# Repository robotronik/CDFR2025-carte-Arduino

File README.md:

# cdfr2025-carte-Arduino
Arduino mega pro Shield for CDFR 2025

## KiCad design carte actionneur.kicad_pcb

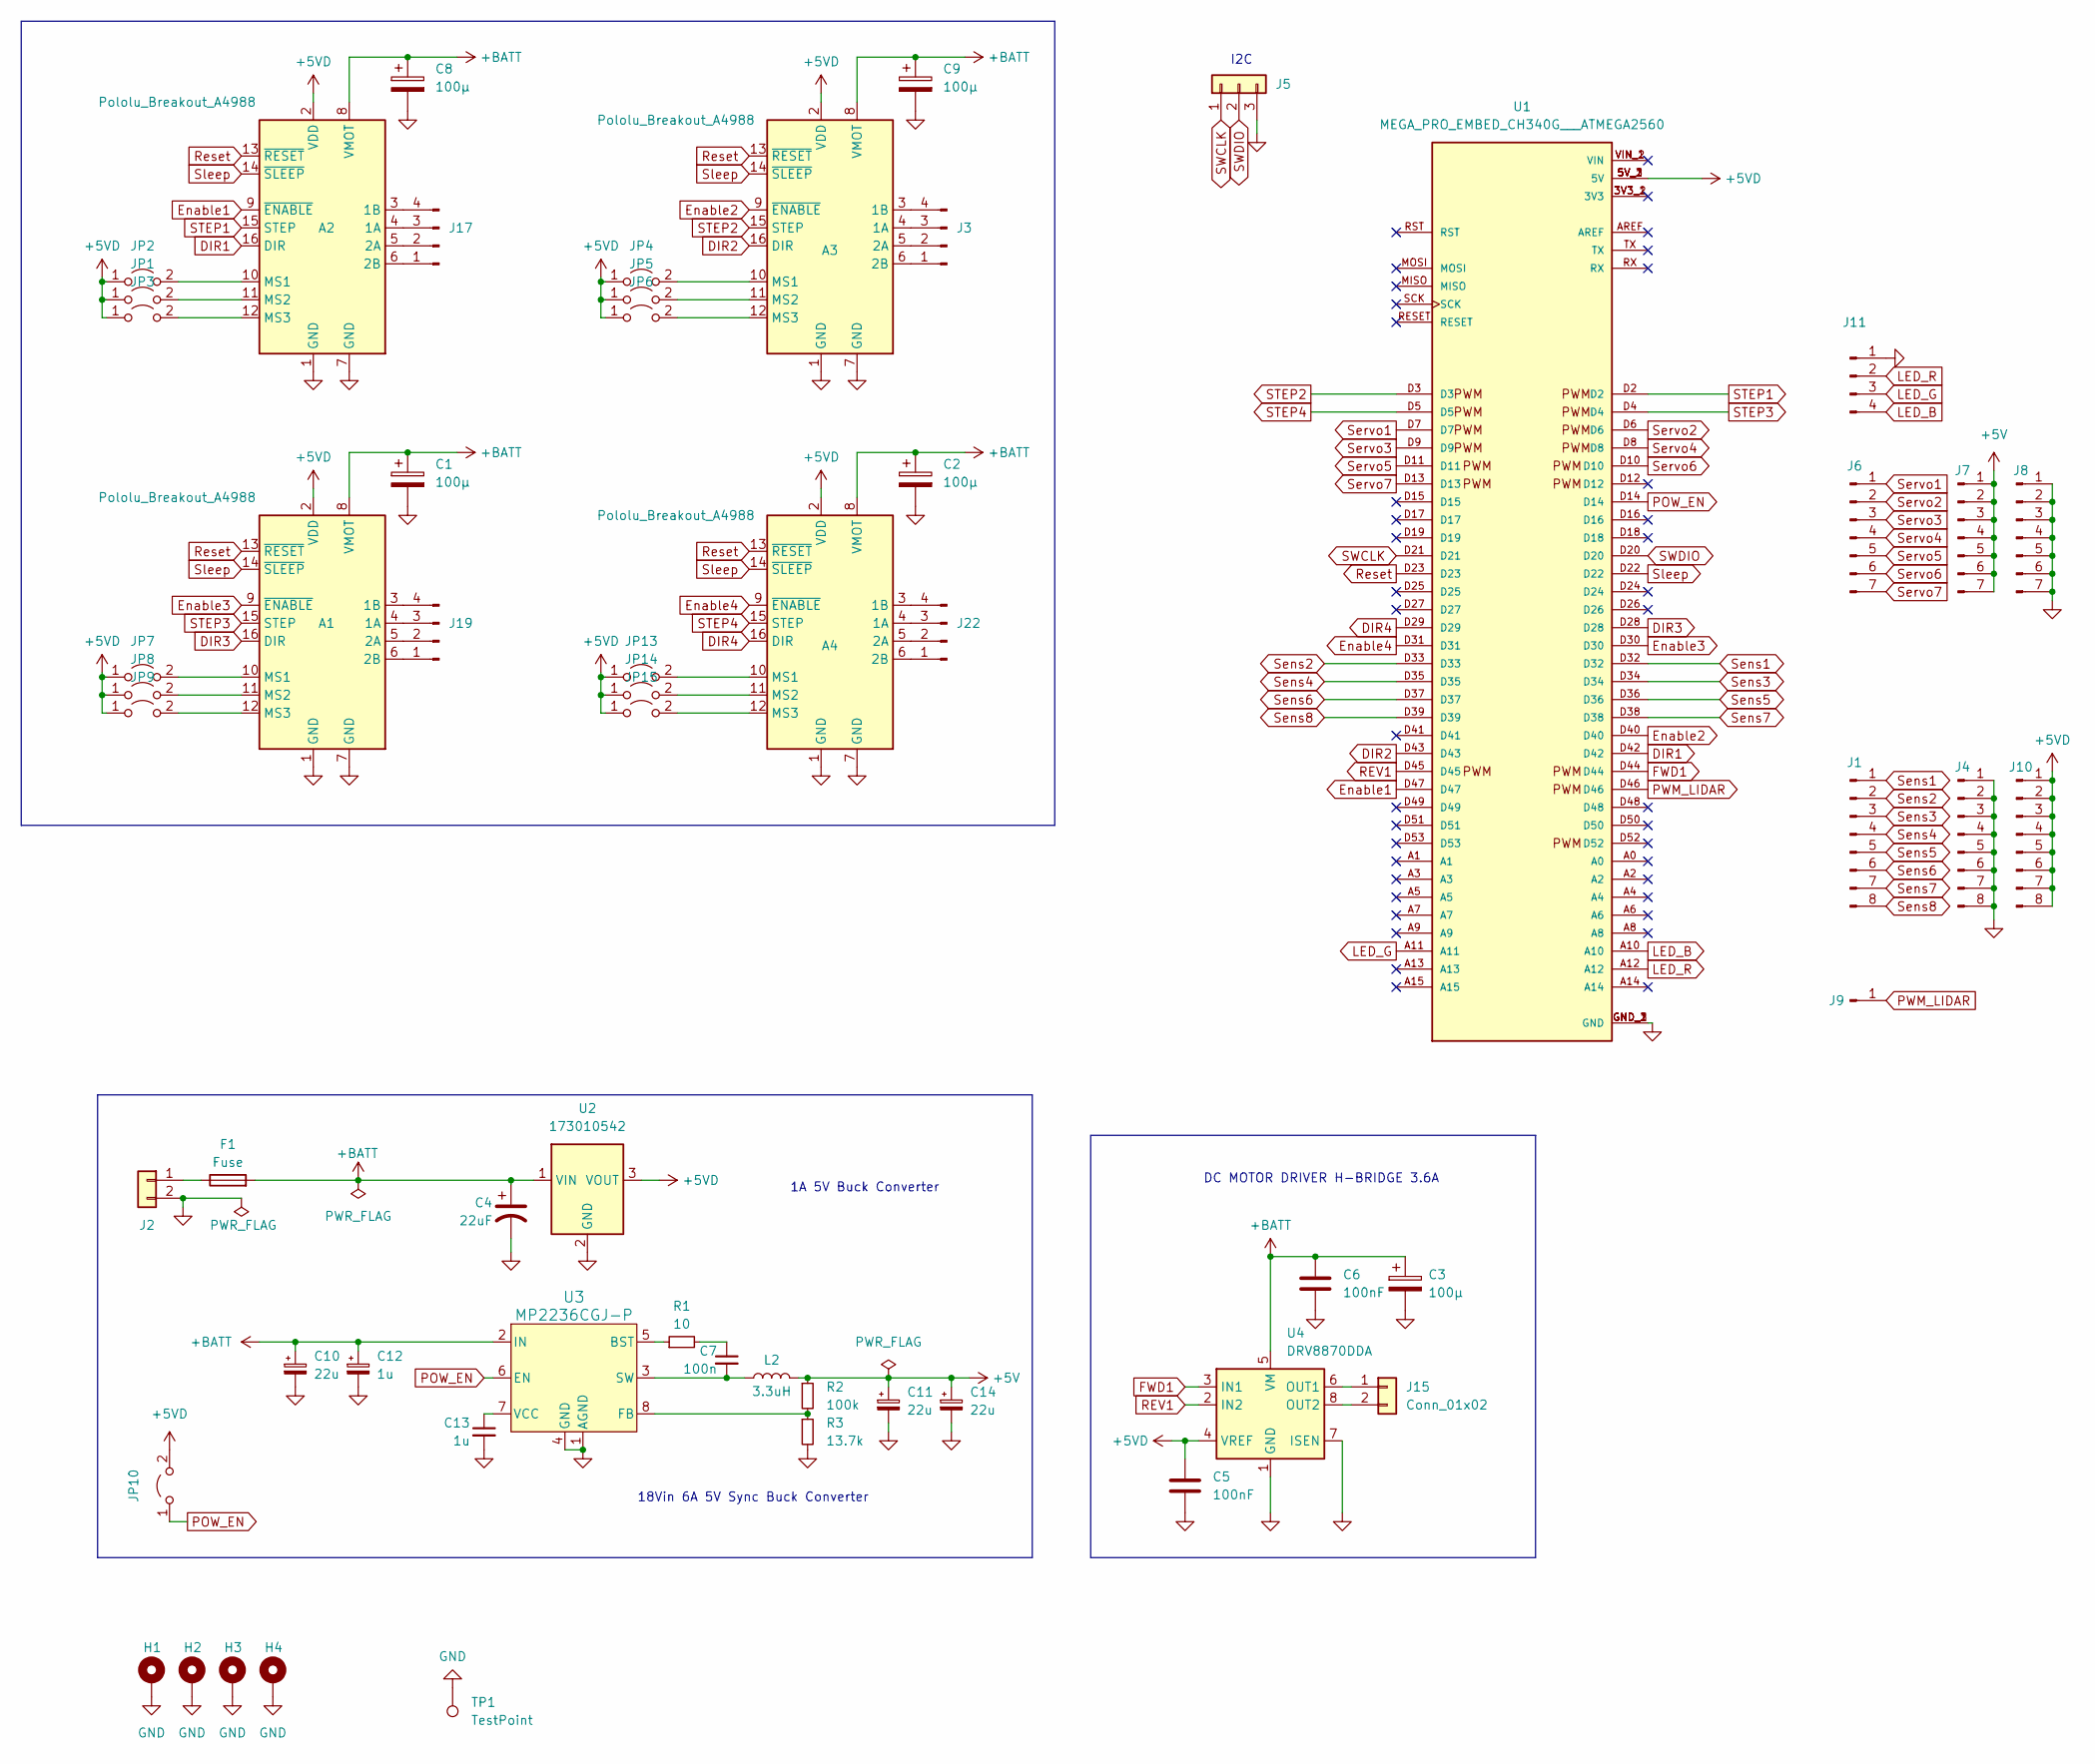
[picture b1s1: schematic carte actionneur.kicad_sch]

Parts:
A1, A2, A3, A4: Pololu_Breakout_A4988; Pololu_Breakout-16_15.2x20.3mm
C1, C2, C3, C8, C9: 100µ; CP_Radial_D8.0mm_P3.50mm
C4: 22uF; C_1206_3216Metric
C5, C6: 100nF; C_0805_2012Metric
C7: 100n; C_1206_3216Metric
C10, C11, C14: 22u; C_1206_3216Metric
C12, C13: 1u; C_1206_3216Metric
F1: Fuse; FUSE_0154004.DR
H1, H2, H3, H4: MountingHole_Pad; MountingHole_3.2mm_M3_Pad_Via
J1, J4, J10: Conn_01x08_Pin; PinHeader_1x08_P2.54mm_Vertical
J2: Conn_01x02; CUI_TBP01R1-508-02BE
J3, J17, J19, J22: Conn_01x04_Pin; JST_XH_B4B-XH-A_1x04_P2.50mm_Vertical
J5: Conn_01x03; JST_XH_B3B-XH-A_1x03_P2.50mm_Vertical
J6, J7, J8: Conn_01x07_Pin; PinHeader_1x07_P2.54mm_Vertical
J9: Conn_01x01_Pin; PinHeader_1x01_P2.54mm_Vertical
J11: Conn_01x04_Pin; PinHeader_1x04_P2.54mm_Vertical
J15: Conn_01x02; JST_XH_B2B-XH-A_1x02_P2.50mm_Vertical
JP1, JP2, JP3, JP4, JP5, JP6, JP7, JP8, JP9, JP10, JP13, JP14, JP15: Jumper_2_Open; SolderJumper-2_P1.3mm_Open_TrianglePad1.0x1.5mm
L2: 3.3uH; L_Coilcraft_XAL6030-XXX
R1: 10; R_1206_3216Metric
R2: 100k; R_1206_3216Metric
R3: 13.7k; R_0805_2012Metric
TP1: TestPoint; TestPoint_Bridge_Pitch2.0mm_Drill0.7mm
U1: MEGA_PRO_EMBED_CH340G___ATMEGA2560; MODULE_MEGA_PRO_EMBED_CH340G___ATMEGA2560; PARTREV 12/May/2017
U2: 173010542; U_Wurth_MagIC-FDSM_173010x42
U3: MP2236CGJ-P; TSOT-23-8
U4: DRV8870DDA; Texas_HTSOP-8-1EP_3.9x4.9mm_P1.27mm_EP2.95x4.9mm_Mask2.4x3.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

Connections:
+5V: C11.1, C14.1, J7.1, J7.2, J7.3, J7.4, J7.5, J7.6, J7.7, L2.2, R2.1
+5VD: A1.2 (VDD), A2.2 (VDD), A3.2 (VDD), A4.2 (VDD), C5.1, J10.1, J10.2, J10.3, J10.4, J10.5, J10.6, J10.7, J10.8, JP1.1 (A), JP2.1 (A), JP3.1 (A), JP4.1 (A), JP5.1 (A), JP6.1 (A), JP7.1 (A), JP8.1 (A), JP9.1 (A), JP10.2 (B), JP13.1 (A), JP14.1 (A), JP15.1 (A), U1.5V_1 (5V), U1.5V_2 (5V), U1.5V_3 (5V), U2.3 (VOUT), U4.4 (VREF)
+BATT: A1.8 (VMOT), A2.8 (VMOT), A3.8 (VMOT), A4.8 (VMOT), C1.1, C2.1, C3.1, C4.1, C6.1, C8.1, C9.1, C10.1, C12.1, F1.2, U2.1 (VIN), U3.2 (IN), U4.5 (VM)
DIR1: A2.16 (DIR), U1.D42
DIR2: A3.16 (DIR), U1.D43
DIR3: A1.16 (DIR), U1.D28
DIR4: A4.16 (DIR), U1.D29
Enable1: A2.9 (~ENABLE), U1.D47
Enable2: A3.9 (~ENABLE), U1.D40
Enable3: A1.9 (~ENABLE), U1.D30
Enable4: A4.9 (~ENABLE), U1.D31
FWD1: U1.D44, U4.3 (IN1)
GND: A1.1 (GND), A1.7 (GND), A2.1 (GND), A2.7 (GND), A3.1 (GND), A3.7 (GND), A4.1 (GND), A4.7 (GND), C1.2, C2.2, C3.2, C4.2, C5.2, C6.2, C8.2, C9.2, C10.2, C11.2, C12.2, C13.2, C14.2, H1.1, H2.1, H3.1, H4.1, J2.2, J4.1, J4.2, J4.3, J4.4, J4.5, J4.6, J4.7, J4.8, J5.3, J8.1, J8.2, J8.3, J8.4, J8.5, J8.6, J8.7, J11.1, R3.2, TP1.1, U1.GND_1 (GND), U1.GND_2 (GND), U1.GND_3 (GND), U2.2 (GND), U3.1 (AGND), U3.4 (GND), U4.1 (GND), U4.7 (ISEN), U4.9 (GND)
LED_B: J11.4, U1.A10
LED_G: J11.3, U1.A11
LED_R: J11.2, U1.A12
unnamed: A1.4 (1A), J19.3
unnamed: A1.3 (1B), J19.4
unnamed: A1.5 (2A), J19.2
unnamed: A1.6 (2B), J19.1
unnamed: A1.10 (MS1), JP7.2 (B)
unnamed: A1.11 (MS2), JP8.2 (B)
unnamed: A1.12 (MS3), JP9.2 (B)
unnamed: A2.4 (1A), J17.3
unnamed: A2.3 (1B), J17.4
unnamed: A2.5 (2A), J17.2
unnamed: A2.6 (2B), J17.1
unnamed: A2.10 (MS1), JP2.2 (B)
unnamed: A2.11 (MS2), JP1.2 (B)
unnamed: A2.12 (MS3), JP3.2 (B)
unnamed: A3.4 (1A), J3.3
unnamed: A3.3 (1B), J3.4
unnamed: A3.5 (2A), J3.2
unnamed: A3.6 (2B), J3.1
unnamed: A3.10 (MS1), JP4.2 (B)
unnamed: A3.11 (MS2), JP5.2 (B)
unnamed: A3.12 (MS3), JP6.2 (B)
unnamed: A4.4 (1A), J22.3
unnamed: A4.3 (1B), J22.4
unnamed: A4.5 (2A), J22.2
unnamed: A4.6 (2B), J22.1
unnamed: A4.10 (MS1), JP13.2 (B)
unnamed: A4.11 (MS2), JP14.2 (B)
unnamed: A4.12 (MS3), JP15.2 (B)
unnamed: C7.1, R1.2
unnamed: F1.1, J2.1
unnamed: J15.1, U4.6 (OUT1)
unnamed: J15.2, U4.8 (OUT2)
unnamed: R1.1, U3.5 (BST)
unnamed: R2.2, R3.1, U3.8 (FB)
unnamed: C7.2, L2.1, U3.3 (SW)
unnamed: C13.1, U3.7 (VCC)
POW_EN: JP10.1 (A), U1.D14, U3.6 (EN)
PWM_LIDAR: J9.1, U1.D46
REV1: U1.D45, U4.2 (IN2)
Reset: A1.13 (~RESET), A2.13 (~RESET), A3.13 (~RESET), A4.13 (~RESET), U1.D23
STEP1: A2.15 (STEP), U1.D2
STEP2: A3.15 (STEP), U1.D3
STEP3: A1.15 (STEP), U1.D4
STEP4: A4.15 (STEP), U1.D5
SWCLK: J5.1, U1.D21
SWDIO: J5.2, U1.D20
Sens1: J1.1, U1.D32
Sens2: J1.2, U1.D33
Sens3: J1.3, U1.D34
Sens4: J1.4, U1.D35
Sens5: J1.5, U1.D36
Sens6: J1.6, U1.D37
Sens7: J1.7, U1.D38
Sens8: J1.8, U1.D39
Servo1: J6.1, U1.D7
Servo2: J6.2, U1.D6
Servo3: J6.3, U1.D9
Servo4: J6.4, U1.D8
Servo5: J6.5, U1.D11
Servo6: J6.6, U1.D10
Servo7: J6.7, U1.D13
Sleep: A1.14 (~SLEEP), A2.14 (~SLEEP), A3.14 (~SLEEP), A4.14 (~SLEEP), U1.D22

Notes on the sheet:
18Vin 6A 5V Sync Buck Converter
1A 5V Buck Converter
I2C
DC MOTOR DRIVER H-BRIDGE 3.6A

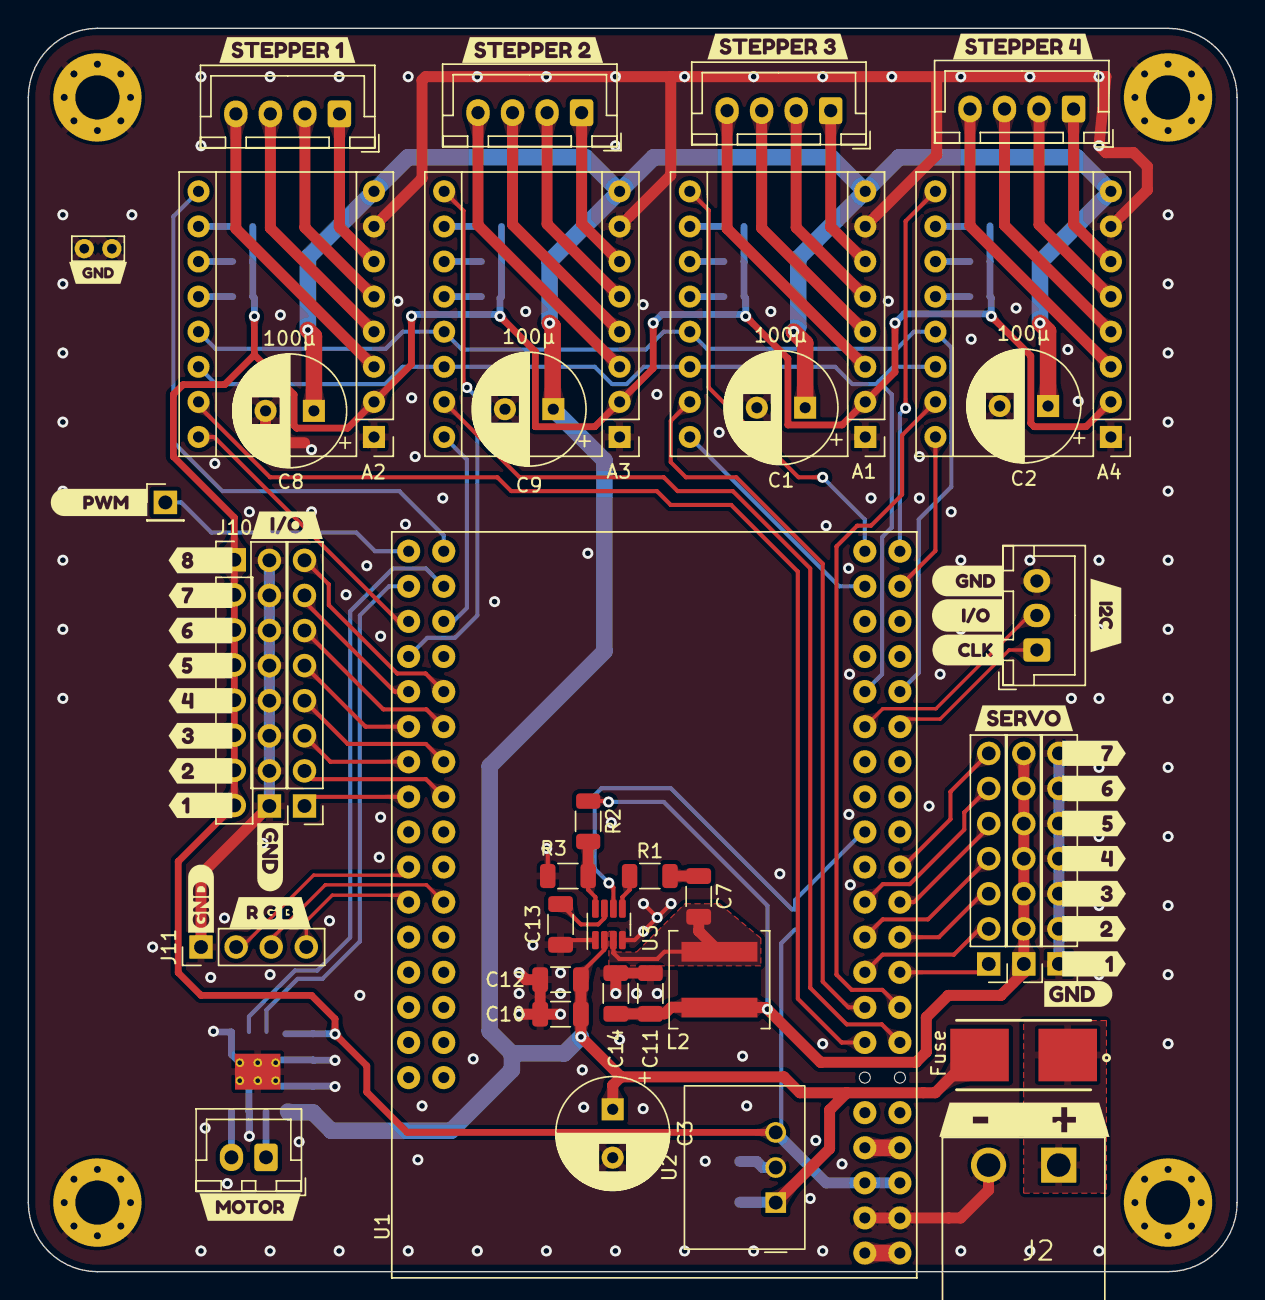
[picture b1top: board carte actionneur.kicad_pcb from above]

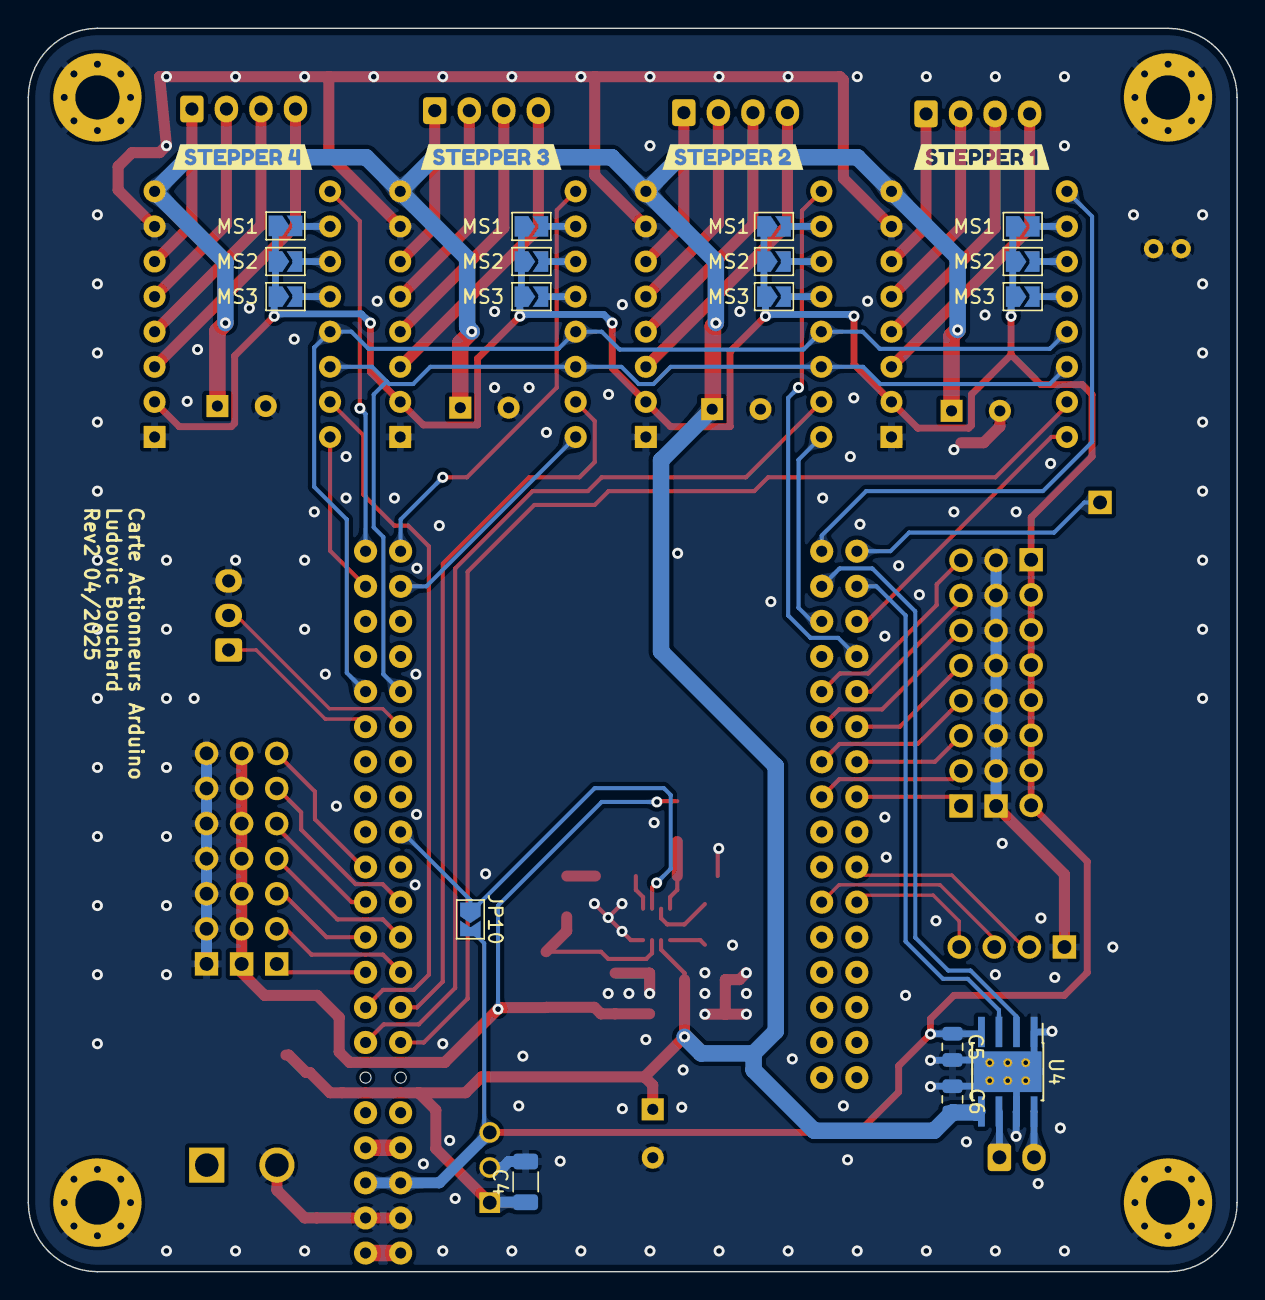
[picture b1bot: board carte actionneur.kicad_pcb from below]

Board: 2 copper layers, 87.5 x 90.0 mm, 97 parts (21 on the bottom side), 78 nets.

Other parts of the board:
kibuzzard-67A0E12F: G***; kibuzzard-67A0E12F
kibuzzard-67A0F0A3: G***; kibuzzard-67A0F0A3
kibuzzard-67A0F0D2: G***; kibuzzard-67A0F0D2
kibuzzard-67A0F0E8: G***; kibuzzard-67A0F0E8
kibuzzard-67A0F0EE: G***; kibuzzard-67A0F0EE
kibuzzard-67A13B87: G***; kibuzzard-67A13B87
kibuzzard-67A14A78: G***; kibuzzard-67A14A78
kibuzzard-67A1464C: G***; kibuzzard-67A1464C
kibuzzard-67A14542: G***; kibuzzard-67A14542
kibuzzard-679EA1D9: G***; kibuzzard-679EA1D9
kibuzzard-679EA1F0: G***; kibuzzard-679EA1F0
kibuzzard-679EA1FA: G***; kibuzzard-679EA1FA
kibuzzard-679EA20F: G***; kibuzzard-679EA20F
kibuzzard-679EA25C: G***; kibuzzard-679EA25C
kibuzzard-679EA204: G***; kibuzzard-679EA204
kibuzzard-679EA208: G***; kibuzzard-679EA208
kibuzzard-679EA213: G***; kibuzzard-679EA213
kibuzzard-679EA236, kibuzzard-679EA236#2, kibuzzard-679EA236#3: G***; kibuzzard-679EA236
kibuzzard-679FD2F5: G***; kibuzzard-679FD2F5
kibuzzard-679FD32C: G***; kibuzzard-679FD32C
kibuzzard-679FD63B: G***; kibuzzard-679FD63B
kibuzzard-679FD63E: G***; kibuzzard-679FD63E
kibuzzard-679FD64B: G***; kibuzzard-679FD64B
kibuzzard-679FD326: G***; kibuzzard-679FD326
kibuzzard-679FD331: G***; kibuzzard-679FD331
kibuzzard-679FD606: G***; kibuzzard-679FD606
kibuzzard-679FD637: G***; kibuzzard-679FD637
kibuzzard-679FD642: G***; kibuzzard-679FD642
kibuzzard-679FD645: G***; kibuzzard-679FD645
kibuzzard-679FD648: G***; kibuzzard-679FD648
kibuzzard-679FD690: G***; kibuzzard-679FD690
kibuzzard-679FDC70: G***; kibuzzard-679FDC70
kibuzzard-679FDCB9: G***; kibuzzard-679FDCB9
kibuzzard-679FDCBD: G***; kibuzzard-679FDCBD
kibuzzard-679FDCC2: G***; kibuzzard-679FDCC2

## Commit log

2024-02-17 Add files via upload
    ''
2024-02-21 test git
2024-02-22 test
2024-02-25 shema complet
2024-02-25 ajout prise capteur
2024-02-29 PCB fini
2024-03-07 modification 3
2025-02-02 dev continues
2025-02-03 modifications 2025
2025-02-03 presque fini
2025-02-03 Finished
2025-02-03 pushed production and libs
2025-02-03 Updated Arduino for 2025 (#1)
2025-03-30 first
2025-03-30 second
2025-03-31 WE models
2025-04-01 final rev2
2025-04-01 Dev/rev2 (#2)
